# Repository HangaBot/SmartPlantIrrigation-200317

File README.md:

# SmartPlantIrrigation-200317
Smart Plant Irrigation System

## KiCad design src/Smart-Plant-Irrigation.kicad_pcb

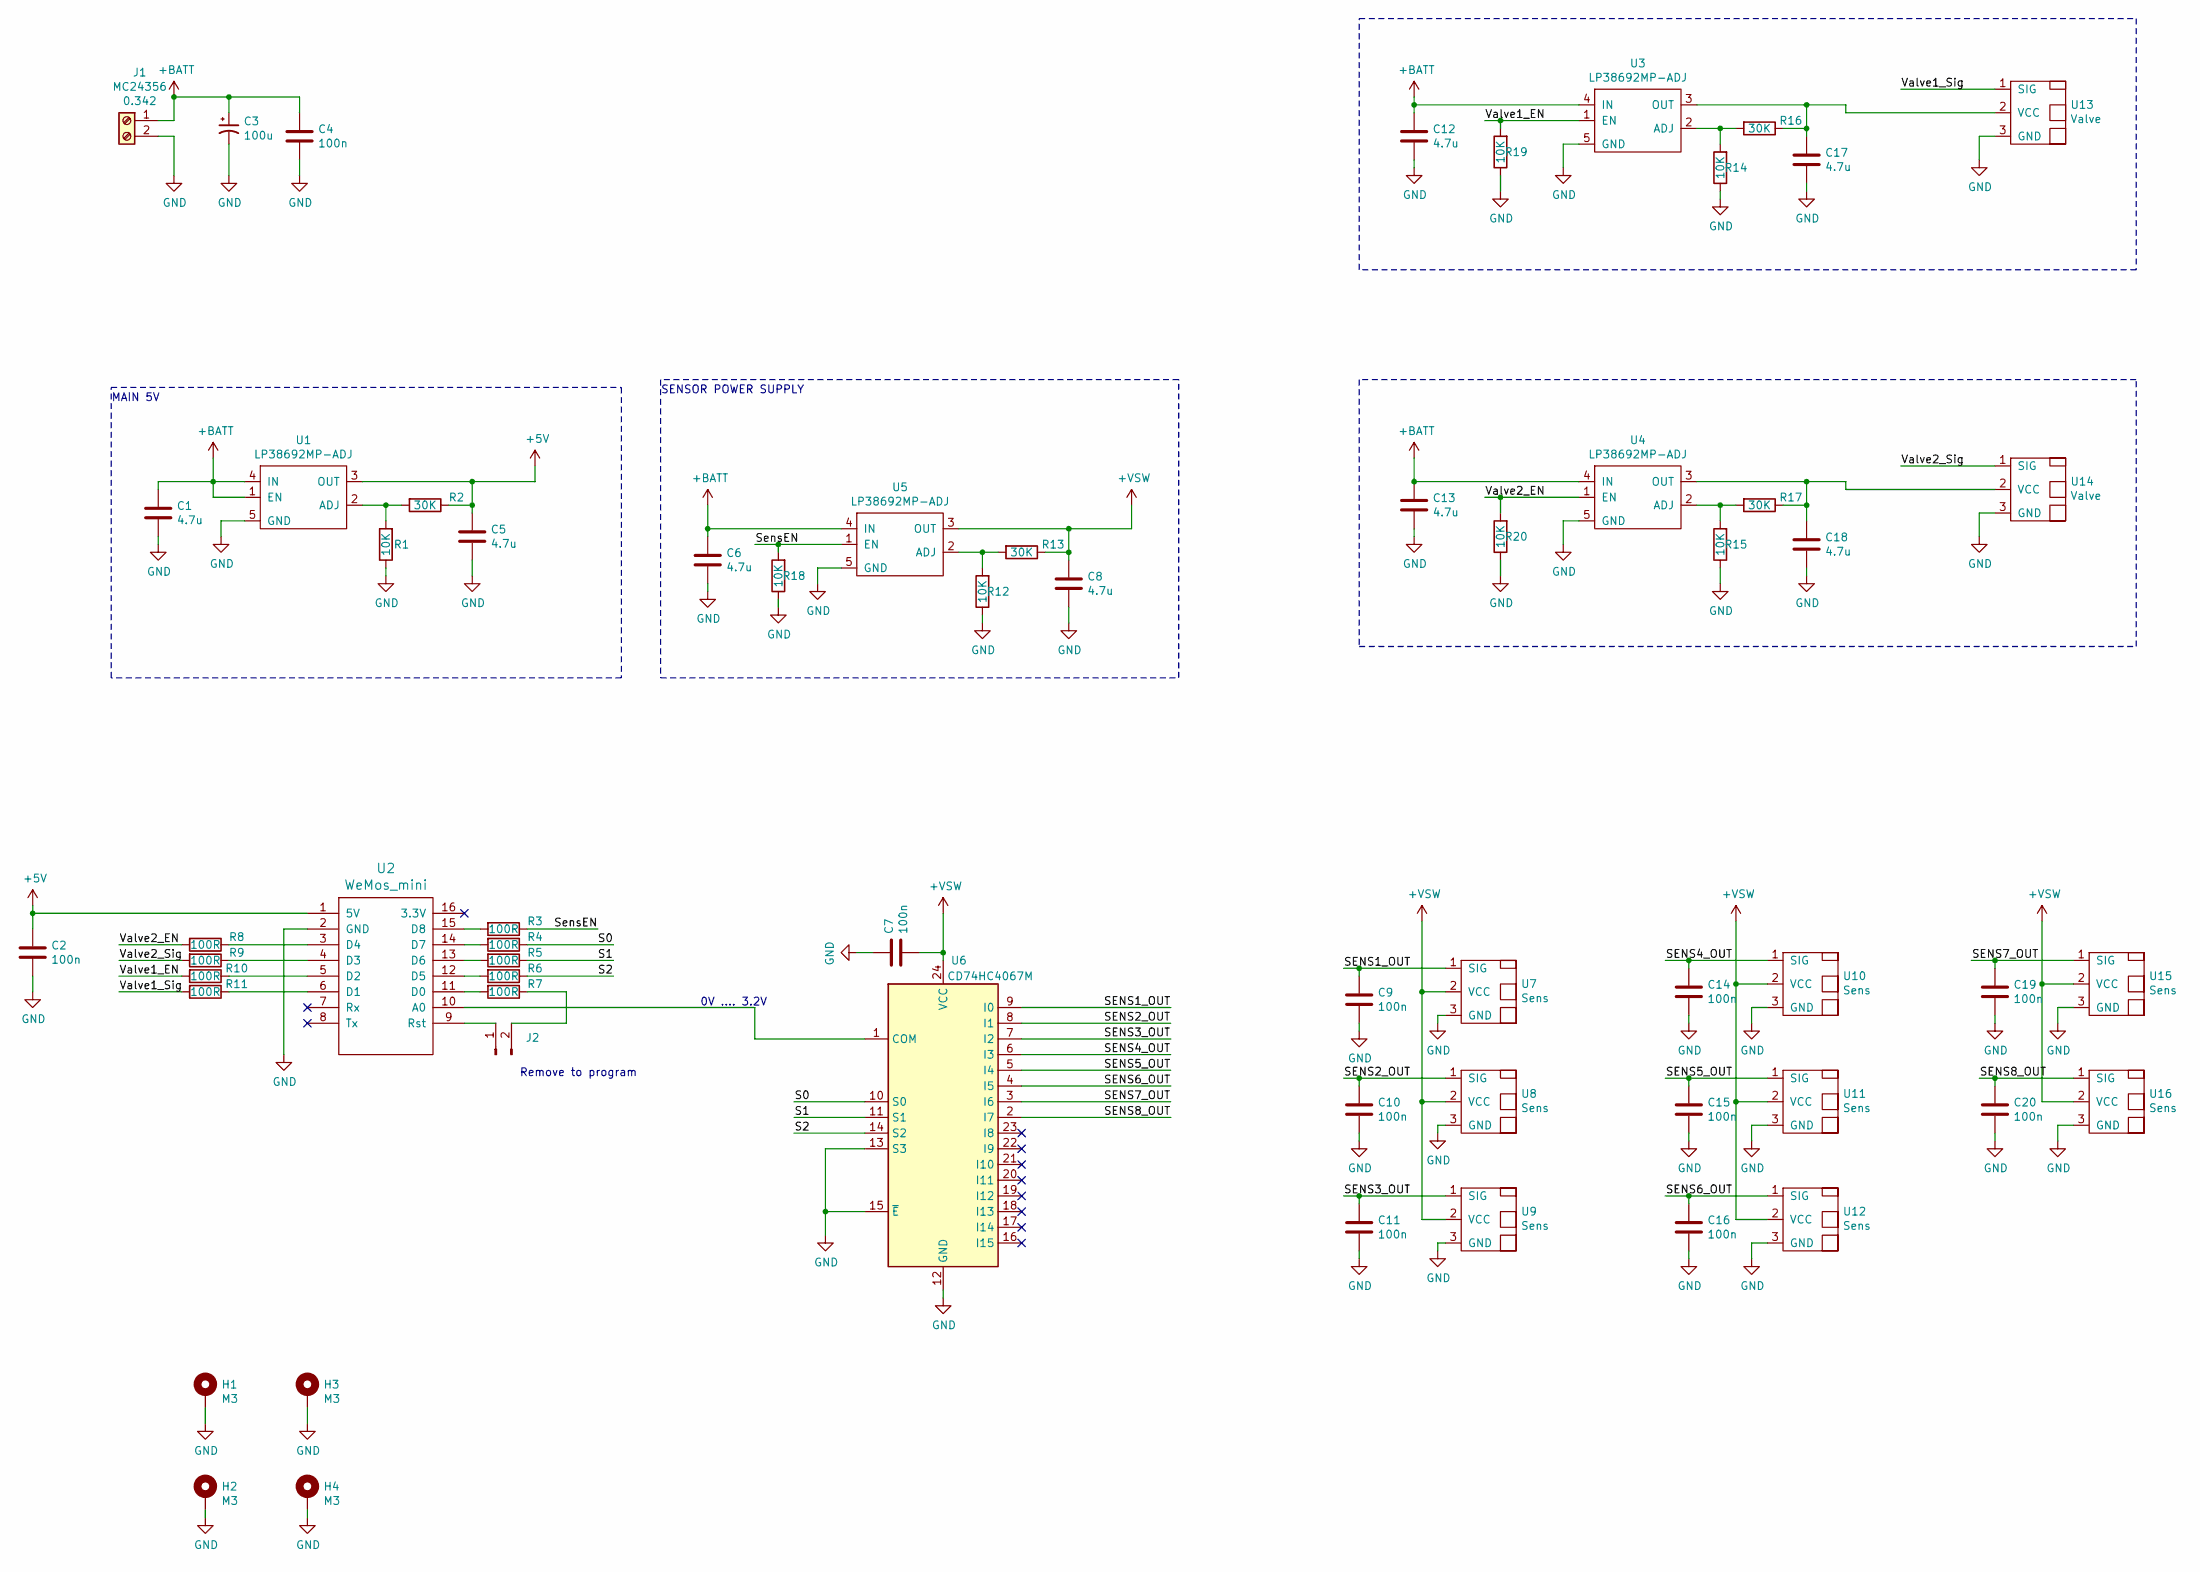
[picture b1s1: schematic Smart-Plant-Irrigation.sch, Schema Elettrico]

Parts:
C1, C5, C6, C8, C12, C13, C17, C18: 4.7u; C_0805_2012Metric; Farnell P/N 1657937
C2, C4, C7, C9, C10, C11, C14, C15, C16, C19, C20: 100n; C_0402_1005Metric; Farnell P/N 2803331
C3: 100u; CP_Elec_6.3x5.8
H1, H2, H3, H4: M3; MountingHole_3.2mm_M3
J1: MC24356; MC24356_ft; Farnell P/N 2396250
J2: Conn_01x02_Male; PinHeader_1x02_P2.54mm_Vertical
R1, R12, R14, R15, R18, R19, R20: 10K; R_0402_1005Metric; Farnell P/N 1738864
R2, R13, R16, R17: 30K; R_0402_1005Metric; Farnell P/N 2140891
R3, R4, R5, R6, R7, R8, R9, R10, R11: 100R; R_0402_1005Metric; Farnell P/N 1469672
U1, U3, U4, U5: LP38692MP-ADJ; SOT-223-5; Mouser P/N 926-38692MP-ADJ/NOPB; Farnell P/N 3007672
U2: WeMos_mini; D1_mini_board
U6: CD74HC4067M; SOIC-24W_7.5x15.4mm_P1.27mm; Farnell P/N 1740161
U7, U8, U9, U10, U11, U12, U15, U16: Sens; Sens_Solder
U13, U14: Valve; Sens_Solder

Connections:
+5V: C2.1, C5.1, R2.1, U1.3 (OUT), U2.1 (5V)
+BATT: C1.1, C3.1, C4.1, C6.1, C12.1, C13.1, J1.1, U1.1 (EN), U1.4 (IN), U3.4 (IN), U4.4 (IN), U5.4 (IN)
+VSW: C7.2, C8.1, R13.1, U5.3 (OUT), U6.24 (VCC), U7.2 (VCC), U8.2 (VCC), U9.2 (VCC), U10.2 (VCC), U11.2 (VCC), U12.2 (VCC), U15.2 (VCC), U16.2 (VCC)
/S0: R4.1, U6.10 (S0)
/S1: R5.1, U6.11 (S1)
/S2: R6.1, U6.14 (S2)
/SENS1_OUT: C9.1, U6.9 (I0), U7.1 (SIG)
/SENS2_OUT: C10.1, U6.8 (I1), U8.1 (SIG)
/SENS3_OUT: C11.1, U6.7 (I2), U9.1 (SIG)
/SENS4_OUT: C14.1, U6.6 (I3), U10.1 (SIG)
/SENS5_OUT: C15.1, U6.5 (I4), U11.1 (SIG)
/SENS6_OUT: C16.1, U6.4 (I5), U12.1 (SIG)
/SENS7_OUT: C19.1, U6.3 (I6), U15.1 (SIG)
/SENS8_OUT: C20.1, U6.2 (I7), U16.1 (SIG)
/SensEN: R3.1, R18.2, U5.1 (EN)
/Valve1_EN: R10.2, R19.2, U3.1 (EN)
/Valve1_Sig: R11.2, U13.1 (SIG)
/Valve2_EN: R8.2, R20.2, U4.1 (EN)
/Valve2_Sig: R9.2, U14.1 (SIG)
GND: C1.2, C2.2, C3.2, C4.2, C5.2, C6.2, C7.1, C8.2, C9.2, C10.2, C11.2, C12.2, C13.2, C14.2, C15.2, C16.2, C17.2, C18.2, C19.2, C20.2, H1.1, H2.1, H3.1, H4.1, J1.2, R1.1, R12.1, R14.1, R15.1, R18.1, R19.1, R20.1, U1.5 (GND), U2.2 (GND), U3.5 (GND), U4.5 (GND), U5.5 (GND), U6.12 (GND), U6.13 (S3), U6.15 (~E), U7.3 (GND), U8.3 (GND), U9.3 (GND), U10.3 (GND), U11.3 (GND), U12.3 (GND), U13.3 (GND), U14.3 (GND), U15.3 (GND), U16.3 (GND)
unnamed: C17.1, R16.1, U3.3 (OUT), U13.2 (VCC)
unnamed: C18.1, R17.1, U4.3 (OUT), U14.2 (VCC)
unnamed: J2.1, U2.9 (Rst)
unnamed: J2.2, R7.1
unnamed: R1.2, R2.2, U1.2 (ADJ)
unnamed: R3.2, U2.15 (D8)
unnamed: R4.2, U2.14 (D7)
unnamed: R5.2, U2.13 (D6)
unnamed: R6.2, U2.12 (D5)
unnamed: R7.2, U2.11 (D0)
unnamed: R8.1, U2.3 (D4)
unnamed: R9.1, U2.4 (D3)
unnamed: R10.1, U2.5 (D2)
unnamed: R11.1, U2.6 (D1)
unnamed: R12.2, R13.2, U5.2 (ADJ)
unnamed: R14.2, R16.2, U3.2 (ADJ)
unnamed: R15.2, R17.2, U4.2 (ADJ)
unnamed: U2.10 (A0), U6.1 (COM)

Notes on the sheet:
0V .... 3.2V
MAIN 5V
SENSOR POWER SUPPLY
Remove to program

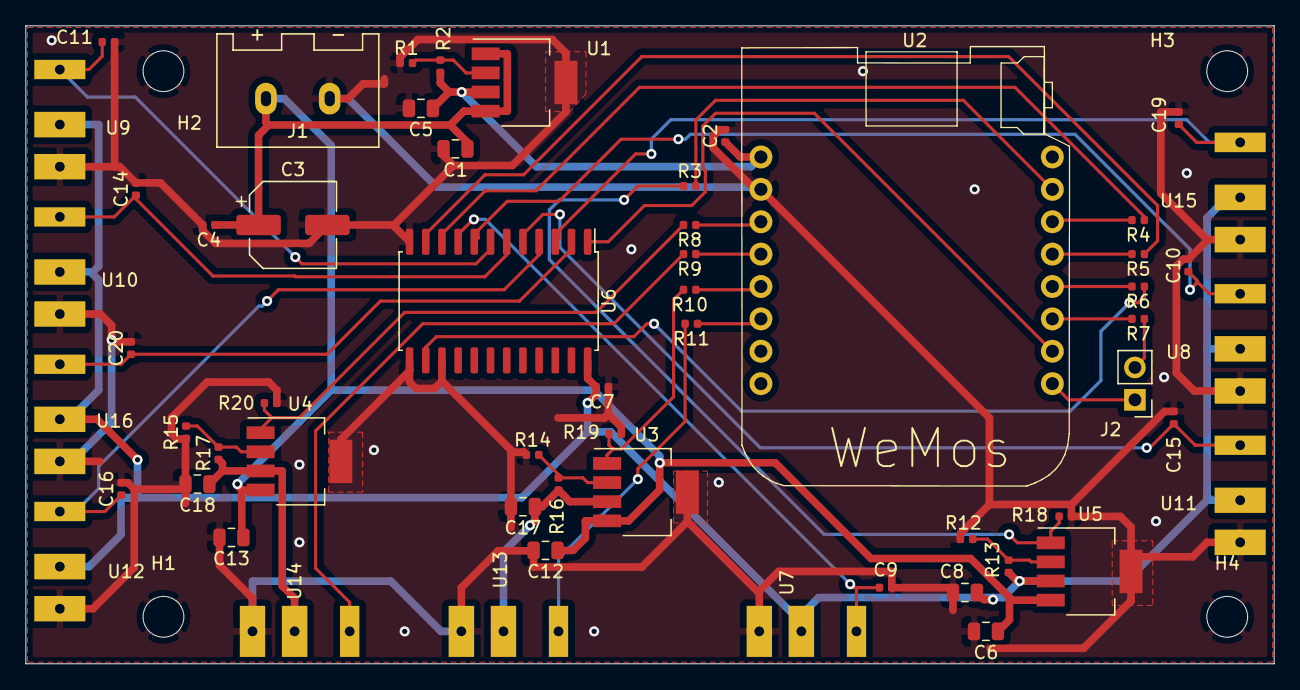
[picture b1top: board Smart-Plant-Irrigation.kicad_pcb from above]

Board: 2 copper layers, 97.9 x 50.0 mm, 62 parts (0 on the bottom side), 38 nets.

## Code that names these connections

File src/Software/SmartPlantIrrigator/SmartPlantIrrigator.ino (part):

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// *****************   GPIO  *********************************************

#define PIN_HUM_ANALOG   A0  // humidity pin
#define VALVE1_EN        D2  // Valve 1 enable signal
#define VALVE2_EN        D4  // Valve 2 enable signal
#define VALVE1_SIG       D1  // Valve 1 command signal (PWM)
#define VALVE2_SIG       D3  // Valve 2 command signal (PWM)

#define SENS_EN          D8  // sensor Enable

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
void setup() {
  context.state = s_setup;
  pinMode(VALVE1_EN, OUTPUT);
  pinMode(VALVE2_EN, OUTPUT);
  pinMode(VALVE1_SIG, OUTPUT);
  pinMode(VALVE2_SIG, OUTPUT);

  pinMode(SENS_EN, OUTPUT);
  pinMode(S0, OUTPUT);
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
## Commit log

2020-05-06 Stato progetto PCB completata software da scrivere
